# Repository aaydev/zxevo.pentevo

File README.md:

# Компьютер-конструктор ZX Evolution     

##### Компьютер-конструктор ZX Evolution!

#### [english](http://nedopc.com/zxevo/zxevo_eng.php)

**ВНИМАНИЕ!** **Изделие поставляется независимым производителем. Обращаться по поводу приобретения к Виталию [tetroid@inbox.ru](mailto:tetroid@inbox.ru).**

- - -

Компьютер конструктор **ZX Evolution** является развитием Spectrum-совместимых компьютеров, но собран на современной элементной базе и под современную периферию.

**Разработка:**  
hardware: Вадим Акимов (LVD), Чунин Роман (CHRV), Дмитриев Дмитрий (DDP);  
software: Вячеслав Савенков (Savelij).

### Характеристики:

*   Z80 3.5 МГц (классический)/ 7 МГц (турбо режим без WAIT)/ 14МГц (мега турбо режим с WAIT);
*   4 МБ ОЗУ, 512КБ ПЗУ;
*   Форм-фактор miniITX (microATX для rev.A и B), 2 слота ZXBUS, питание ATX или +5,+12В;
*   Гибкая архитектура, основанная на fpga (EP1K50);
*   Периферийный контроллер ATMEGA128;
*   PS/2 интерфейс клавиатуры и мыши;
*   Интерфейсы Floppy (1818ВГ93), IDE (один канал, два устройства master/slave), SD(HC) карта, RS232;
*   Видеовыходы RGB, VGA (аппаратный скандаблер);
*   Звуковые интерфейсы AY, Beeper, Covox (аппаратный ШИМ);
*   Поддержка механической клавиатуры и джойстика;
*   Поддержка Tape интерфейса (магнитофонный вход/выход);
*   Энергонезависимые часы/календарь.

Список мониторов протестированных на совместимость с ZX Evolution в VGA режиме [здесь](http://svn.nedopc.com/dl.php?repname=pentevo&path=%2Fdocs%2Fsupported_monitors.pdf).

Тестовая программа для PC для тестирования монитора на совместимость [здесь](http://nedopc.com/zxevo/tools/zxevo_vga_test_20100221.rar).

### Документация:

**_Форум поддержки пользователей_** [здесь](http://forum.nedopc.com/).

Принципиальная схема (revision C) [здесь](http://nedopc.com/zxevo/zxevo_sch_revc.pdf).

Монтажная схема (revision C) [здесь](http://nedopc.com/zxevo/zxevo_mon_revc.pdf).

Cписок деталей (revision C) [здесь](http://nedopc.com/zxevo/zxevo_bom_revc.pdf).

Руководство пользователя (revision C) [здесь](http://nedopc.com/zxevo/zxevo_user_manual_revc.pdf).

Руководство по сборке платы (revision C) [здесь](http://nedopc.com/zxevo/zxevo_solder_revc.pdf).

Документация для производства (revision C) [здесь](http://nedopc.com/zxevo/zxevo_revc.zip) \[PCAD2002\] (использование в коммерческих целях только по договоренности с представителями [NedoPC](http://nedopc.com/aboutus.php)).

**ЦЕНЫ:** [здесь](http://nedopc.com/catalog.php).

**Внимание!**  
Описание стартового меню (EVO RESET SERVICE), документация программиста (для конфигурации BASECONF) и документация по процедуре обновления прошивок (BOOTLOADER) находится в таблице **"Прошивки и Документация"**

### Прошивки и Документация:

|     |     |     |     |     |     |
| --- | --- | --- | --- | --- | --- |
| **Название** | **Версия** | **Назначение** | **Документация** | **Файлы** | **SVN** |
| **_EVO RESET SERVICE FE,  <br>EVO DOS FE,  <br>EVO PROF_** | latest | Улучшен эмулятор дисководов, теперь он работает с неизменной пзу TR-DOS.  <br>Для работы требуется соответствующая прошивка FPGA  <br>Стартовое меню, сервисные расширения и ZX ПЗУ.  <br>Предназначена для прошивки в ROM.  <br>_Прошивку можно произвести из предыдущей версии или с помощью **TEST&SERVICE**._  <br>Поддержка: Savelij. | [Описание сервис-прошивки ''EVO Reset Service''.pdf](http://svn.nedopc.com/filedetails.php?repname=pentevo&path=%2Fdocs%2F%D0%9E%D0%BF%D0%B8%D1%81%D0%B0%D0%BD%D0%B8%D0%B5+%D1%81%D0%B5%D1%80%D0%B2%D0%B8%D1%81-%D0%BF%D1%80%D0%BE%D1%88%D0%B8%D0%B2%D0%BA%D0%B8+%27%27EVO+Reset+Service%27%27.pdf) |     | [zxevo\_fe.rom](http://svn.nedopc.com/filedetails.php?repname=pentevo&path=%2From%2Fzxevo_fe.rom) |
| **_BASECONF FE_** | latest | Основная рабочая конфигурация (от NedoPC).  <br><br>*   Поддержка эмуляции портов дисковода/ВГ93, для использования этой фичи нужен ROM zxevo\_fe.rom.<br>*   Добавлена палитра DDP без ШИМа (alone).<br>*   Ускорена работа процессора на 14 МГц (psk7).<br><br>Предназначена для прошивки в ATMEGA128.  <br>_Прошивка производится с помощью **BOOTLOADER**._  <br>Поддержка: CHRV (ATMEGA128), LVD (EP1K50QC208). | [zxevo\_base\_configuration.odt](http://svn.nedopc.com/filedetails.php?repname=pentevo&path=%2Fdocs%2Fzxevo_base_configuration.odt)<br><br>[zxevo\_base\_configuration.pdf](http://svn.nedopc.com/filedetails.php?repname=pentevo&path=%2Fdocs%2Fzxevo_base_configuration.pdf) |     | [zxevo\_fw.bin](http://svn.nedopc.com/filedetails.php?repname=pentevo&path=%2Fcfgs%2Fstandalone_base_trdemu%2Ftrunk%2Fzxevo_fw.bin) |
| **_BOOTLOADER_** | 2012.01.24 | Загружает и обновляет рабочие конфигурации.  <br>Предназначена для прошивки в ATMEGA128.  <br>_Прошивка производится с помощью программатора._  <br>Поддержка: DDp. | [zxevo\_firmware\_update.pdf](http://nedopc.com/zxevo/rom/zxevo_firmware_update.pdf) | [bootloader20120124.zip](http://nedopc.com/zxevo/rom/bootloader20120124.zip) | [zxevo\_bl.hex](http://svn.nedopc.com/filedetails.php?repname=pentevo&path=%2Favrboot%2Ftrunk%2Favr%2Fzxevo_bl.hex)<br><br>[zxevo\_bl.e2p](http://svn.nedopc.com/filedetails.php?repname=pentevo&path=%2Favrboot%2Ftrunk%2Favr%2Fzxevo_bl.e2p)<br><br>[read\_me.txt](http://svn.nedopc.com/filedetails.php?repname=pentevo&path=%2Favrboot%2Ftrunk%2Fread_me.txt) |
| **_TEST&SERVICE_** | 2016.01.04 | Cервисная конфигурация для тестирования и настройки ZXEvo. Полезная конфигурация для тех кто сам собирает ZXEvo.  <br>Предназначена для прошивки в ATMEGA128.  <br>_Прошивка производится с помощью **BOOTLOADER**._  <br>Поддержка: DDp. | [zxevo\_testservice.pdf](http://nedopc.com/zxevo/rom/zxevo_testservice.pdf)  <br>[zxevo\_testservice\_flash.pdf](http://nedopc.com/zxevo/rom/zxevo_testservice_flash.pdf) | [testservice20160104.zip](http://nedopc.com/zxevo/rom/testservice20160104.zip) | [zxevo\_fw.bin](http://svn.nedopc.com/filedetails.php?repname=pentevo&path=%2Ftest_n_service%2Ftrunk%2Frus%2Fzxevo_fw.bin) |

Зеркало исходников (SVN) доступно на сайте [**ZXEVO.RU**.](http://svn.zxevo.ru/listing.php?repname=pentevo)

### Прошивки сторонних разработчиков:

**ВНИМАНИЕ:** Вопросы по поддержке прошивок задавайте непосредственно авторам прошивок. NedoPC не несет ответственности за ошибки или недоработки в прошивках сторонних разработчиков.

|     |     |     |     |     |
| --- | --- | --- | --- | --- |
| **Название** | **Версия** | **Назначение** | **Документация** | **Файлы** |
| [**_ZXEVO TS_**](http://forum.tslabs.info/viewtopic.php?f=12&t=20) |     | ZXEVO TS конфигурация с поддержкой спрайтов и оригинальных расширенных видеорежимов. Полноценная рабочая конфигурации отличается не только схемой, но и ROM. Также под нее созданы специализированное утилиты, игры и прочее ПО. [Подробности здесь.](http://forum.tslabs.info/viewtopic.php?f=12&t=20) | [FAQ](http://forum.tslabs.info/viewtopic.php?f=12&t=157) | [Инструкция по установке конфигурации.](http://forum.nedopc.com/viewtopic.php?f=30&t=622&start=652) |
| **_ScorpEvo_** | 6.1 (05.11.2011) | Scorpion Evolution (ScorpEvo) задуман как полноценная альтернатива (в дальнейшем – замена) самого знаменитого и в то же время противоречивого петербургского компьютера «Scorpion ZS 256 turbo+» Сергея Зонова. | [scorpevo.pdf](http://nedopc.com/zxevo/scorpion/scorpevo.pdf) | [scorpevo061.zip](http://nedopc.com/zxevo/scorpion/scorpevo061.zip)  <br>[svn scorpevo](http://svn.nedopc.com/listing.php?repname=pentevo&path=%2Fscorpevo%2F) |

- - -

### История версий:

**Revision C:**  
Изменения от предыдущей версии:

*   Форм фактор miniITX (172x170mm);
*   Убран PAL кодер;
*   Добавлен принтерный интерфейс по стандарту AY-принтер;
*   Добавлено управление множителем частоты;
*   Добавлены аудиовходы (всего 3 аудиовхода);
*   Используется процессор Z80 в QFP корпусе;
*   Убран отдельный RGB разъем (все выведено на VGA);
*   Добавлен RS232-USB мост;
*   Убран AT разъем питания;
*   Добавлен разъем для подключения PAL кодера.

**Revision B:**  
Изменения от предыдущей версии:

*   Исправлен шаблон PS/2 клавиатуры-мыши;
*   Исправлен ОЕ на ICS501;
*   Увеличена площадь радиатора 78M05;
*   Добавлен джампер регулирующий присутствие 12V на слотах;
*   Добавлены направляющие для разъема ATX питания;
*   Увеличены контактные площадки дросселей;
*   Уменьшен размер платы;
*   Убран джампер разрешающий програмирование контроллера;
*   Сделано для диодов 4148 универсальная площадка (на смд и выводные);
*   Для ZXBUS сделан указатель 1-го вывода;
*   Исправлена ошибка сброса ВГ93 (завел VG\_RES на D19);
*   Сделан ключ разъема FDD как на ПЦ платах (5-ый контакт);
*   Добавлены на плату надписи "HDD Led", "PWR Led", "ZX Keyboard/ZX Joystick", "Slot1", "Slot2";
*   Перемещен разъем VGA, чтобы был паралельно RGB-out.

Принципиальная схема (revision B) [здесь](http://nedopc.com/zxevo/zxevo_sch_revb.pdf).

Монтажная схема (revision B) [здесь](http://nedopc.com/zxevo/zxevo_mon_revb.pdf).

Cписок деталей (revision B) [здесь](http://nedopc.com/zxevo/zxevo_bom_revb.pdf).

Доработка для работы с принтером [AY-printer](http://nedopc.com/zxevo/zxevo_ay_printer.pdf).

Руководство пользователя (revision B) [здесь](http://nedopc.com/zxevo/zxevo_user_manual_revb.pdf).

Руководство по сборке платы (revision B) [здесь](http://nedopc.com/zxevo/zxevo_solderind_and_start_revb.pdf).

Документация для производства (revision B) [здесь](http://nedopc.com/zxevo/zxevo_revb.zip) \[PCAD2002\] (использование в коммерческих целях только по договоренности с представителями [NedoPC](http://nedopc.com/aboutus.php)).

**Revision A:**  
Первая версия - экспериментальная, только у разработчиков.

Принципиальная схема (revision A) [здесь](http://nedopc.com/zxevo/zxevo_sch_reva.pdf).

Монтажная схема (revision A) [здесь](http://nedopc.com/zxevo/zxevo_mon_reva.pdf).

Cписок деталей (revision A) [здесь](http://nedopc.com/zxevo/zxevo_detali_reva.pdf).

Документация для производства (revision A) [здесь](http://nedopc.com/zxevo/zxevo_reva.zip) \[PCAD2002\] (использование в коммерческих целях только по договоренности с представителями [NedoPC](http://nedopc.com/aboutus.php)).

- - -

Email: [nedopc@mail.ru](mailto:nedopc@mail.ru), [nedopc@yandex.ru](mailto:nedopc@yandex.ru).

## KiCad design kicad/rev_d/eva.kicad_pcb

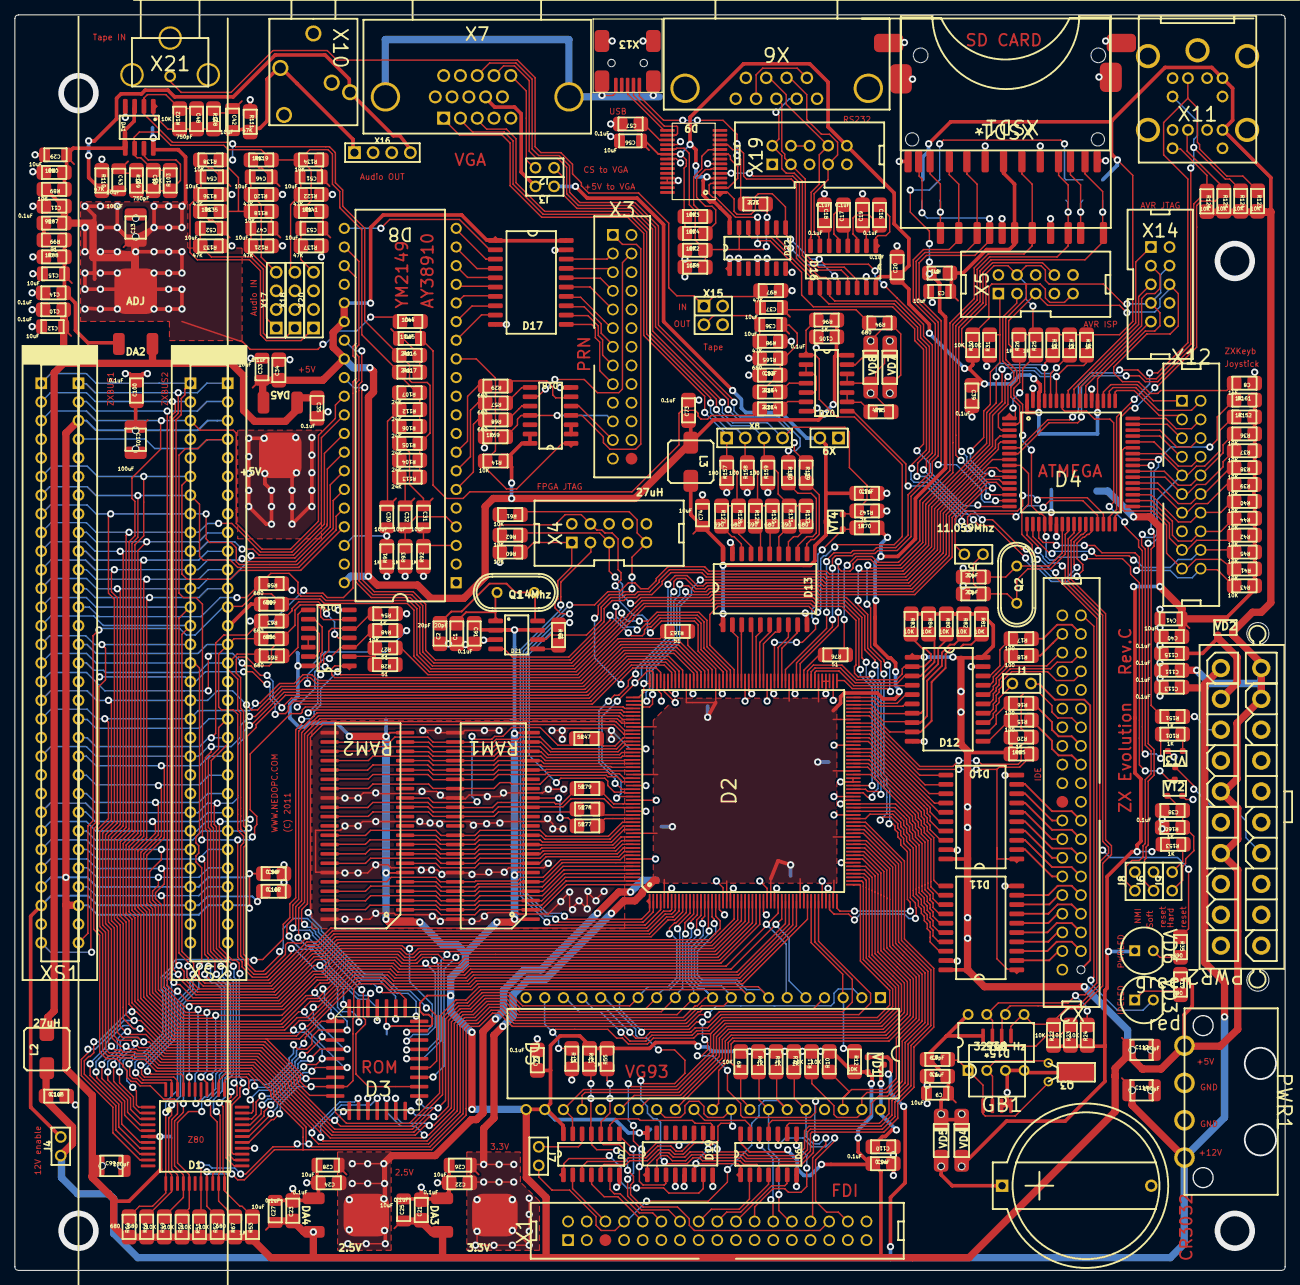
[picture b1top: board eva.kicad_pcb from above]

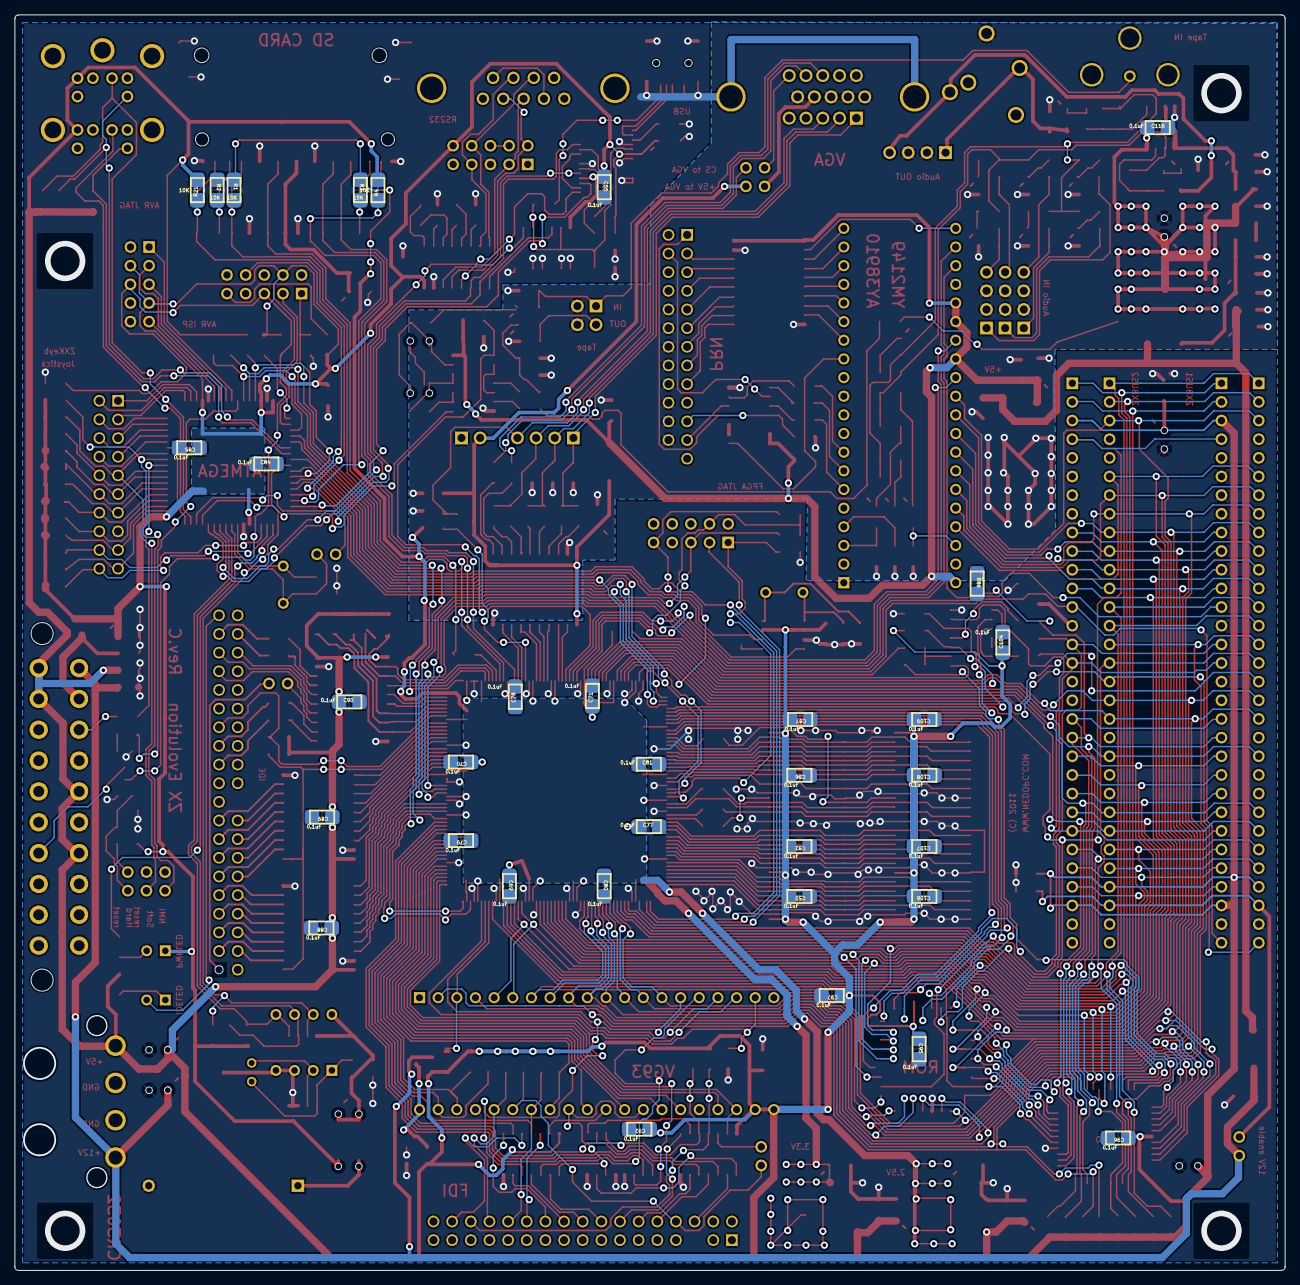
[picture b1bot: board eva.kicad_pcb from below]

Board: 2 copper layers, 173.0 x 171.0 mm, 338 parts (34 on the bottom side), 412 nets.

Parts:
C1, C2, C4, C5: 20pF; C-CHIP
C3, C9, C12, C15, C25, C26, C27, C28, C29, C30, C31, C32, C33, C36, C37, C41, C42, C43, C45, C46, C47, C51, C52, C53, C54, C56, C74: 10uF; EC-CHIP
C6, C10, C11, C14, C16, C17, C18, C19, C20, C21, C22, C23, C24, C34, C35, C38, C39, C40, C50, C55, C57, C69, C70, C71, C73, C76, C77, C78, C79, C80, C81, C82, C83, C84, C85, C86, C87, C88, C89, C90, C91, C92, C93, C94, C95, C96, C97, C98, C100, C102, C103, C104, C105, C106, C107, C108, C109, C110, C111, C113, C115, C116: 0.1uF; C-CHIP
C7: 6.8pF; C-CHIP
C8, C58: 1nF; C-CHIP
C13, C99, C101, C112, C114: 100uF; EC-CHIPB
C44: 10nF; C-CHIP
C48, C49: 750pF; C-CHIP
D1: QFP44X8
D2: PQFP208X5
D3: PLCC32
D4: TQFP64X8
D5, D8: DIP40
D6, D7, D20: SO14
D9: SSOP28
D10, D11, D12: SOL20
D13, D17: 74hct245; SOL20
D14: 74ACT04; SO14
D15: DIP8
D15*: PCF8583T
D16, D19: SO16
D18: 74HCT04; SO14
D21: SO8
D22: 74HCT125; SO14
DA1: SO8
DA2: ADJ; DPAK
DA3: 3.3V; DPAK
DA4: 2.5V; DPAK
DA5: +5V; DPAK
GB1: CR3032; BAT_Primary
J1, J2, J3, J4, J5, J6, J7, J8, J9: JUMPER_JUMPER(Primary)
L1: 1uH; L-CHIP
L2, L3: 27uH; CDR64B
PWR1: THP_4MR
PWR2: ATXPOWER
Q1: 14Mhz; CRYSTAL_QUARTZ(Primary)
Q2: 11.059Mhz; CRYSTAL_QUARTZ(Primary)
Q3: 32768 Hz; 32768
R1, R2, R3, R4, R9, R10, R11, R12, R14, R21, R22, R23, R24, R30, R31, R36, R37, R38, R39, R40, R41, R42, R43, R44, R45, R48, R49, R50, R51, R52, R60, R61, R62, R72, R73, R74, R80, R81, R82, R83, R84, R85, R89, R90, R102, R103, R118, R119, R123, R124, R125, R126, R134, R135, R138, R141: 10K; R-CHIP
R5, R6, R7, R8, R13, R20, R25, R26, R32, R33, R34, R53, R54, R55, R69, R70, R88, R91, R92, R93, R96, R101, R151, R152, R153, R160, R161: 1K; R-CHIP
R15, R16, R17, R18, R157, R158, R159: 100; R-CHIP
R19, R35, R127, R129, R131: 390; R-CHIP
R27, R28, R46, R47, R76, R77, R78, R79, R108, R109, R163: 51; R-CHIP
R29, R56, R57, R58, R59, R63, R64, R65, R66, R67, R68, R94, R128, R130, R132, R165: 680; R-CHIP
R71, R114, R164: 2.2K; R-CHIP
R86: 1; R-CHIP
R87, R99: 91; R-CHIP
R95, R97, R98, R110, R111, R120, R121, R122, R133, R136, R137: 47K; R-CHIP
R104, R105, R106, R107, R112, R113, R116, R117: 24K; R-CHIP
R139, R140, R142: 75; R-CHIP
RAM1, RAM2: SOJ42
VD1, VD2: SOT-23
VD3: red; LED100_LED(Primary)
VD4, VD5, VD7, VD8: LL4148
VD6: green; LED100_LED(Primary)
VT2, VT3, VT4: SOT-23
X1: FDD34M
X2: IDE40M
X3: IDC26
X4, X5, X14, X19: IDC10M
X6: DSUB-9
X7: DB15VGA
X8, X16, X17, X18, X20: PLB1-4I
X9: PLB1-2
X10: AYout; ST-214C
X11: MDD-6FR
X12: IDC20
X13: MINI-USB
X15: PLB2-2
X21: RSA103
XS1, XS2: SLOT62_ZXSLOT(Primary)
XSD1: SDC09W4
XSD1*: SD01-AP0003

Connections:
A0: D1.27, D2.44, D3.12, XS1.A9, XS2.A9
A1: D1.28, D2.41, D3.11, XS1.A10, XS2.A10
A2: D1.29, D2.40, D3.10, XS1.A11, XS2.A11
A3: D1.30, D2.39, D3.9, XS1.A12, XS2.A12
A4: D1.31, D2.38, D3.8, XS1.A24, XS2.A24
A5: D1.32, D2.37, D3.7, D5.5, XS1.A23, XS2.A23
A6: D1.34, D2.36, D3.6, D5.6, XS1.A22, XS2.A22
A7: D1.35, D2.31, D3.5, XS1.A21, XS2.A21
A8: D1.36, D2.30, D3.27, XS1.B26, XS2.B26
A9: D1.37, D2.29, D3.26, XS1.A27, XS2.A27
A10: D1.38, D2.28, D3.23, XS1.B27, XS2.B27
A11: D1.40, D2.27, D3.25, XS1.A28, XS2.A28
A12: D1.41, D2.26, D3.4, XS1.A2, XS2.A2
A13: D1.42, D2.25, D3.28, XS1.B2, XS2.B2
A14: D1.43, D2.24, XS1.A1, XS2.A1
A15: D1.44, D2.19, XS1.B1, XS2.B1
AGND: C10.2, C11.2, C12.2, C13.2, C14.2, C15.2, C29.2, C33.2, C34.2, C35.2, C73.2, C74.2, C76.2, C83.1, C105.2, C116.2, D8.1, D8.24, D13.10, D13.19, D17.10, D17.19, D18.7, D20.7, DA1.4, DA5.2, R69.1, R86.1, R88.1, R90.1, R91.1, R92.1, R93.1, R97.1, R98.1, R110.1, R111.1, R120.1, R121.1, R122.1, R133.1, R136.1, R137.1, R142.1, R157.1, R158.1, R159.1, R165.2, X3.10, X3.12, X3.14, X3.16, X3.18, X3.20, X3.22, X3.24, X7.6, X7.7, X7.8, X7.10, X7.11, X9.1, X10.1, X15.2, X15.4, X16.2, X16.3, X17.2, X17.3, X18.2, X18.3, X20.2, X20.3, X21.2, X21.3, X21.4
ATX_POWERON: R101.1, VT3.1
AVCC5: C33.1, C34.1, C73.1, C105.1, D8.25, D8.26, D8.28, D8.40, D17.1, D17.20, D18.13, D18.14, D20.14, DA5.3, L3.2, R14.1, R96.1
AVCC8: C11.1, C13.1, C44.1, C116.1, DA1.8, DA2.2, R87.2, R89.2
AYA0: D8.21, D17.2
AYA1: D8.20, D17.3
AYA2: D8.19, D17.4
AYA3: D8.18, D17.5
AYA4: D8.17, D17.6
AYA5: D8.16, D17.7
AYA6: D8.15, D17.8
AYA7: D8.14, D17.9
AYB0: D8.13, D18.1, R14.2
AYB5: D8.8, R29.2
AYB6: D8.7, R57.2
AYB7: D8.6, R68.2
AY_BC1: D2.136, D8.29
AY_BDIR: D2.135, D8.27
AY_CLK: D2.134, D8.22
BEEP: D2.133, D20.1, R96.2
CHA: C32.2, D8.4, R93.2
CHB: C31.2, D8.3, R92.2
CHC: C30.2, D8.38, R91.2
CLKZ: D1.1, R28.1
CLKZ_IN: D2.79, R27.1
CLKZ_OUT: D14.1, R163.2
CONFDONE: D2.2, D4.59, R34.2
CSROM: D2.150, D14.5, R54.2
CTS: D16.8, X6.8, X19.8
CTS_TTL: D4.16, D9.3, D22.11
D0: D1.9, D2.18, D3.13, D5.7, D8.37, XS1.B6, XS2.B6
D1: D1.10, D2.17, D3.14, D5.8, D8.36, XS1.B7, XS2.B7
D2: D1.7, D2.16, D3.15, D5.9, D8.35, XS1.B8, XS2.B8
D3: D1.3, D2.15, D3.17, D5.10, D8.34, XS1.B11, XS2.B11
D4: D1.2, D2.14, D3.18, D5.11, D8.33, XS1.B12, XS2.B12
D5: D1.4, D2.13, D3.19, D5.12, D8.32, XS1.B10, XS2.B10
D6: D1.5, D2.12, D3.20, D5.13, D8.31, XS1.B9, XS2.B9
D7: D1.8, D2.11, D3.21, D5.14, D8.30, XS1.B3, XS2.B3
DAT1: R2.2, XSD1.8, XSD1*.8
DAT2: R3.2, XSD1.9, XSD1*.9
DIR: D5.16, D6.3
FCLK: D2.183, R46.1
GND: C1.1, C2.1, C3.2, C4.1, C5.1, C6.1, C8.1, C9.2, C18.1, C19.2, C20.2, C21.2, C22.2, C23.2, C24.2, C25.2, C26.2, C27.2, C28.2, C38.2, C39.2, C40.2, C41.2, C50.1, C55.2, C56.2, C57.2, C58.1, C69.2, C70.2, C71.2, C77.2, C78.2, C79.2, C80.2, C81.2, C82.1, C84.2, C85.2, C86.1, C87.1, C88.2, C89.2, C90.2, C91.2, C92.2, C93.2, C94.2, C95.2, C96.2, C97.2, C98.2, C99.2, C100.2, C101.2, C102.2, C103.2, C104.2, C106.1, C107.1, C108.1, C109.1, C110.1, C111.2, C112.2, C113.2, C114.2, C115.2, D1.26, D2.6, D2.20, D2.23, D2.32, D2.35, D2.43, D2.49, D2.59, D2.76, D2.81, D2.82, D2.107, D2.108, D2.109, D2.117, D2.123, D2.129, D2.137, D2.145, D2.151, D2.154, D2.171, D2.181, D2.188, D3.16, D4.22, D4.53, D4.63, D5.20, D5.37, D6.7, D7.7, D9.7, D9.18, D9.21, D9.25, D9.26, D10.10, D10.19, D11.10, D11.19, D12.10, D12.19, D14.7, D15.3, D15.4, D15*.3, D15*.4, D16.15, D19.4, D19.5, D19.8, D21.3, D22.1, D22.2, D22.4, D22.5, D22.7, DA3.1, DA4.1, GB1.2, J6.1, J8.1, PWR1.2, PWR1.3, PWR2.3, PWR2.5, PWR2.7, PWR2.13, PWR2.15, PWR2.16, PWR2.17, Q3.3, R13.2, R31.1, R54.1, R58.1, R59.1, R60.2, R72.1, R86.2, R160.2, RAM1.22, RAM1.29, RAM1.37, RAM1.42, RAM2.22, RAM2.29, RAM2.37, RAM2.42, VT2.2, VT3.2, X1.1, X1.3, X1.7, X1.9, X1.11, X1.13, X1.15, X1.17, X1.19, X1.21, X1.23, X1.25, X1.27, X1.29, X1.31, X1.33, X2.2, X2.19, X2.22, X2.24, X2.26, X2.30, X2.40, X4.2, X4.10, X5.2, X5.10, X6.5, X6.10, X6.11, X7.16, X7.17, X11.3, X11.9, X11.13, X11.14, X11.15, X11.16, X11.17, X12.15, X13.5, X13.6, X13.7, X13.8, X13.9, X14.2, X14.10, X19.5, XS1.A6, XS1.A7, XS1.A14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
IA0: D12.15, X2.35
IA1: D12.14, X2.33
IA2: D12.16, X2.36
ID0: D10.9, X2.17
ID1: D10.7, X2.15
ID2: D10.5, X2.13
ID3: D10.3, X2.11
ID4: D11.9, X2.9
ID5: D11.7, X2.7
ID6: D11.5, X2.5
ID7: D11.3, X2.3
ID8: D11.2, X2.4
ID9: D11.4, X2.6
ID10: D11.6, X2.8
ID11: D11.8, X2.10
ID12: D10.2, X2.12
ID13: D10.4, X2.14
ID14: D10.6, X2.16
ID15: D10.8, X2.18
IDE_A0: D2.104, D12.5
IDE_A1: D2.103, D12.6
IDE_A2: D2.111, D12.4
IDE_D0: D2.96, D10.11
IDE_D1: D2.94, D10.13
IDE_D2: D2.92, D10.15
IDE_D3: D2.89, D10.17
IDE_D4: D2.87, D11.11
IDE_D5: D2.85, D11.13
IDE_D6: D2.75, D11.15
IDE_D7: D2.73, D11.17
IDE_D8: D2.71, D11.18
IDE_D9: D2.74, D11.16
IDE_D10: D2.83, D11.14
IDE_D11: D2.86, D11.12
IDE_D12: D2.88, D10.18
IDE_D13: D2.90, D10.16
IDE_D14: D2.93, D10.14
IDE_D15: D2.95, D10.12
IDE_DIR: D2.97, D10.1, D11.1, R85.2
IDE_RDY: D2.99, R20.1, X2.27
ILED: VD3.K, X2.39
IORQGE1: D2.78, R58.2, XS1.A13
IORQGE2: D2.80, R59.2, XS1.A31, XS2.A13
JOYD: D4.43, R41.2, X12.19
JOYF: D4.19, R43.2, X12.20
JOYL: D4.34, R44.2, X12.16
JOYR: D4.33, R42.2, X12.17
JOYU: D4.18, R45.2, X12.18
LOUT: C42.2, R111.2, X10.5, X16.1
NET00000: C110.2, D5.40, VD1.3
NET00001: C46.1, R119.1
NET00002: D2.189, R78.2
NET00003: C2.2, D21.8, Q1.A
NET00004: D2.190, R77.2
NET00005: D20.4, R164.2
NET00006: D2.168, R47.2
NET00007: D2.139, R163.1
NET00008: X6.4, X6.6
NET00009: R19.2, VD3.A
NET00010: X19.4, X19.6
NET00011: C47.1, R118.1
NET00012: C1.2, D21.1, Q1.B
NET00013: D14.2, R27.2, R28.2
NET00014: D4.17, R35.1
NET00015: J2.1, X7.15
NET00016: R35.2, VD6.K
NET00017: D7.12, J7.0
NET00018: C46.2, R120.2, X17.4
NET00019: D20.6, R114.2
NET00020: D2.114, R76.2
NET00021: C47.2, R121.2, X17.1
NET00022: C51.2, R122.2, X18.4
NET00023: C52.2, R133.2, X18.1
NET00024: D4.58, R101.2
NET00025: C48.1, DA1.2, R102.2, R104.1, R105.1, R113.1, R116.1, R118.2, R135.2, R138.1
NET00026: C48.2, DA1.1, R102.1, R108.2
NET00027: R87.1, R99.2
NET00028: D20.11, D20.12, R95.2, VD7.2, VD8.1
NET00029: D21.5, R46.2
NET00030: D20.9, D20.10, R95.1
NET00031: C49.1, DA1.6, R103.2, R106.1, R107.1, R112.1, R117.1, R119.2, R134.2, R141.1
NET00032: C49.2, DA1.7, R103.1, R109.2
NET00033: C51.1, R134.1
NET00034: C32.1, R104.2, R113.2
NET00035: C37.1, R94.2
NET00036: D14.8, R65.1
NET00037: D9.16, X13.2
NET00038: D20.13, R94.1, VD7.1, VD8.2
NET00039: D18.6, R29.1
NET00040: D18.8, R57.1
NET00041: C10.1, C12.1, C35.1, DA2.3, DA5.1, L2.1
NET00042: C52.1, R135.1
NET00043: D18.10, R68.1
NET00044: D2.186, R79.2
NET00045: C30.1, R107.2, R112.2
NET00046: C14.1, C15.1, DA2.1, R88.2, R99.1
NET00047: C31.1, R105.2, R106.2
NET00048: C42.1, R108.1
NET00049: C43.1, R109.1
NET00050: J9.1, R153.1
NET00051: C53.2, R137.2, X20.4
NET00052: C54.2, R136.2, X20.1
NET00053: C17.2, D16.5
NET00054: C17.1, D16.4
NET00055: C16.2, D16.3
NET00056: C16.1, D16.1
NET00057: C18.2, D16.6
NET00058: C19.1, D16.2
NET00059: C54.1, R138.2
NET00060: C44.2, C45.2, R114.1
NET00061: C45.1, R116.2, R117.2
NET00062: C53.1, R141.2
NET00063: C38.1, J9.0, R160.1, VT2.1
NET00064: D12.13, J1.0
NET00065: R71.1, X13.1
NET00066: D9.15, X13.3
NET00067: GB1.1, VD5.1
NET00068: D12.17, R18.2
NET00069: D13.11, R139.2
NET00070: D13.12, R140.2
NET00071: D4.40, R151.2
NET00072: PWR2.14, VT3.3
NET00074: D16.12, D22.9
NET00075: D18.2, D18.3
NET00076: D12.18, R17.2
NET00077: D16.9, D22.12
NET00078: D9.2, D9.9
NET00079: C57.1, D9.17
NET00080: D9.6, R74.2
NET00081: D9.10, R73.2
NET00085: J3.1, X7.9
NET00087: C36.1, C83.2, R164.1, R165.1
NET00100: D14.11, D14.12
NET00101: D14.4, R63.1
NET00105: D12.11, R15.2
NET00106: D14.10, D14.13
NET00107: D12.12, R16.2
NMIKEY: D4.41, J8.0, R161.1
OUT_B: R131.1, R132.1, R159.2, X7.3, X8.3
OUT_CS: J2.0, R142.2, VT4.2, X8.4
OUT_G: R129.1, R130.1, R158.2, X7.2, X8.2
OUT_HS: R140.1, X7.13
OUT_R: R127.1, R128.1, R157.2, X7.1, X8.1
OUT_VS: R139.1, X7.14
PLLS0: D4.4, D21.6
PLLS1: D4.5, D21.4
PRGDI: D4.2, R30.2, X5.9
PRGDO: D4.3, X5.3
PRGEXCLOCK: J5.1, X5.8
PRN_D0: D17.18, X3.3
PRN_D1: D17.17, X3.5
PRN_D2: D17.16, X3.7
PRN_D3: D17.15, X3.9
PRN_D4: D17.14, X3.11
PRN_D5: D17.13, X3.13
PRN_D6: D17.12, X3.15
PRN_D7: D17.11, X3.17
PR_BUSY: D18.11, R69.2, X3.21
PR_ERR: D18.9, X3.4
PR_PE: D18.5, X3.23
PR_STRB: D18.4, X3.1
PS2_KEYB_CLK: D4.6, R124.1, X11.5
PS2_KEYB_DAT: D4.31, R123.1, X11.1
PS2_MOUS_CLK: D4.7, R126.1, X11.11
PS2_MOUS_DAT: D4.32, R125.1, X11.7
PWRGOOD: PWR2.8, R151.1
RA0: D2.177, RAM1.17, RAM2.17
RA1: D2.175, RAM1.18, RAM2.18
RA2: D2.173, RAM1.19, RAM2.19
RA3: D2.170, RAM1.20, RAM2.20
RA4: D2.169, RAM1.23, RAM2.23
RA5: D2.172, RAM1.24, RAM2.24
RA6: D2.174, RAM1.25, RAM2.25
RA7: D2.176, RAM1.26, RAM2.26
RA8: D2.179, RAM1.27, RAM2.27
RA9: D2.180, RAM1.28, RAM2.28
RD0: D2.208, RAM1.2, RAM2.2
RD1: D2.206, RAM1.3, RAM2.3
RD2: D2.204, RAM1.4, RAM2.4
RD3: D2.202, RAM1.5, RAM2.5
RD4: D2.199, RAM1.7, RAM2.7
RD5: D2.197, RAM1.8, RAM2.8
RD6: D2.195, RAM1.9, RAM2.9
RD7: D2.192, RAM1.10, RAM2.10
RD8: D2.191, RAM1.33, RAM2.33
RD9: D2.193, RAM1.34, RAM2.34
RD10: D2.196, RAM1.35, RAM2.35
RD11: D2.198, RAM1.36, RAM2.36
RD12: D2.200, RAM1.38, RAM2.38
RD13: D2.203, RAM1.39, RAM2.39
RD14: D2.205, RAM1.40, RAM2.40
RD15: D2.207, RAM1.41, RAM2.41
RES: D2.142, D14.3, R48.2
ROMPG2: D2.164, D3.2
ROMPG3: D2.163, D3.30
ROMPG4: D2.162, D3.1
ROUT: C43.2, R110.2, X10.2, X16.4
RS: D3.29, R65.2, XS1.A16, XS2.A16
RTC_PWR: C6.2, C7.1, C9.1, D15.8, D15*.8, VD4.2, VD5.2
RTC_X1: C7.2, D15.1, D15*.1, Q3.1
RTC_X2: D15.2, D15*.2, Q3.2
RTS: D16.7, X6.7, X19.7
RTS_TTL: D4.30, D9.11, D16.10
RXD: D16.13, X6.2, X19.2
RXD_TTL: D4.27, D9.1, D22.8
SCL: D4.25, D15.6, D15*.6, R23.2
SDA: D4.26, D15.5, D15*.5, R22.2
SDCLK: R76.1, XSD1.5, XSD1*.5
SDDET: D4.15, R4.1, XSD1.11, XSD1*.11
SDDI: D2.115, R1.2, XSD1.7, XSD1*.7
SDDO: D2.116, XSD1.2, XSD1*.2
SDWPR: D4.14, R21.1, XSD1.12, XSD1*.10
SPICK: D2.155, D2.184, D4.11, R31.2, X5.1
SPIDI: D2.158, D4.13
SPIDO: D2.156, D2.157, D4.12
STEP: D2.46, D5.15, D6.5
TAPE_BIT: D4.29, D20.8
TAPE_IN: C37.2, R97.2, X15.1, X21.1
TAPE_OUT: C36.2, R98.2, X15.3
TCK_AVR: D4.57, X14.1
TCK_FPGA: D2.1, R60.1, X4.1
TDI_AVR: D4.54, X14.9
TDI_FPGA: D2.153, R61.1, X4.9
TDO_AVR: D4.55, X14.3
TDO_FPGA: D2.4, X4.3
TMS_AVR: D4.56, X14.5
TMS_FPGA: D2.50, R62.1, X4.5
TXD: D16.14, X6.3, X19.3
TXD_TTL: D4.28, D9.5, D16.11
USB_ENA: C58.2, D9.19, D22.10, D22.13, R71.2, R72.2
VB+: D13.14, R131.2
VB-: D13.13, R132.2
VCC2V5: C24.1, C28.1, C78.1, C79.1, C80.1, C81.1, D2.21, D2.33, D2.48, D2.72, D2.77, D2.91, D2.106, D2.124, D2.130, D2.152, D2.185, D2.201, DA4.2
VCC3V3: C22.1, C26.1, C69.1, C70.1, C71.1, C77.1, D2.5, D2.22, D2.34, D2.42, D2.51, D2.66, D2.84, D2.98, D2.110, D2.118, D2.138, D2.146, D2.165, D2.178, D2.194, DA3.2, L1.1, R1.1, R2.1, R3.1, R61.2, R62.2, R70.2, X4.4
VCC5: C21.1, C23.1, C25.1, C27.1, C50.2, C82.2, C86.2, C87.2, C88.1, C89.1, C90.1, C91.1, C92.1, C93.1, C94.1, C95.1, C96.1, C97.1, C98.1, C99.1, C100.1, C101.1, C104.1, C106.2, C107.2, C108.2, C109.2, C111.1, C112.1, D1.6, D3.32, D5.21, D5.22, D6.14, D7.14, D10.20, D11.20, D12.1, D12.20, D14.14, D19.16, D21.2, D21.7, DA3.3, DA4.3, PWR1.1, PWR2.4, PWR2.6, PWR2.19, PWR2.20, R4.2, R5.1, R6.1, R7.1, R8.1, R9.2, R10.2, R11.2, R12.2, R19.1, R20.2, R21.2, R32.1, R33.1, R34.1, R48.1, R49.1, R50.1, R51.1, R52.1, R53.1, R55.2, R64.1, R66.1, R67.1, R80.1, R81.1, R82.1, R83.1, R84.1, R85.1, R123.2, R124.2, R125.2, R126.2, RAM1.1, RAM1.6, RAM1.21, RAM2.1, RAM2.6, RAM2.21, VD1.2, VD2.2, X11.4, X11.10, XS1.A3, XS1.A29, XS1.B28, XS2.A3, XS2.A29, XS2.B28
VCC5_MEGA: C20.1, C39.1, C40.1, C41.1, C55.1, C56.1, C84.1, C85.1, D4.21, D4.52, D4.62, D4.64, D9.4, D9.20, D16.16, D22.14, R22.1, R23.1, R24.1, R25.2, R26.2, R30.1, R36.1, R37.1, R38.1, R39.1, R40.1, R41.1, R42.1, R43.1, R44.1, R45.1, R73.1, R74.1, R152.2, R153.2, R161.2, VD2.3, VD4.1, VD6.A, X5.4, X14.4, X14.7, X19.10
VCC5_STBY: C115.1, PWR2.9, VD2.1
VCC12: C103.1, C113.1, C114.1, J4.0, L2.2, PWR1.4, PWR2.10, VD1.1
VCC12S: C102.1, J4.1, XS1.B29, XS2.B29
VCCSD: C3.1, L1.2, XSD1.4, XSD1*.4
VCSYNC: D2.122, R70.1, VT4.1
VG+: D13.16, R129.2
VG-: D13.15, R130.2
VG_A0: D2.69, D19.1
VG_A1: D2.70, D19.2
VG_CLK: D2.56, D5.24
VG_DRQ: D2.63, D5.38, R10.1
VG_DS0: D7.3, D19.11
VG_DS1: D7.5, D19.10
VG_DS2: D7.9, D19.9
VG_DS3: D7.1, D19.7
VG_HRDY: D2.55, D5.23, D7.13
VG_IRQ: D2.64, D5.39, R11.1
VG_MOT: D5.28, D5.32, D6.1, D19.6
VG_RAWR: D2.58, D5.27
VG_RCLK: D2.57, D5.26
VG_SIDE: D2.65, D6.11
VG_SL: D2.47, D5.17
VG_SR: D2.53, D5.18
VG_TR43: D2.60, D5.29
VG_WD: D2.61, D5.31
VG_WF_DE: D2.62, D5.33, R9.1
VG_WRD: D2.67, D6.9
VHSYNC: D2.121, D13.8
VIDEOVCC: C74.1, C76.1, D13.1, D13.20, J3.0, L3.1, VT4.3, X9.2
VIRTGND: C29.1, DA1.3, DA1.5, R89.1, R90.2
VR+: D13.18, R127.2
VR-: D13.17, R128.2
VVSYNC: D2.120, D13.9
V_B+: D2.126, D13.6
V_B-: D2.125, D13.7
V_G+: D2.128, D13.4
V_G-: D2.127, D13.5
V_R+: D2.132, D13.2
V_R-: D2.131, D13.3
WG: D5.30, D6.13
XTAL1: C5.2, D4.24, J5.0, Q2.B
XTAL2: C4.2, D4.23, Q2.A
ZXCOL0: D4.35, R40.2, X12.14
ZXCOL1: D4.36, R39.2, X12.13
ZXCOL2: D4.37, R38.2, X12.12
ZXCOL3: D4.38, R37.2, X12.11
ZXCOL4: D4.39, R36.2, X12.10
ZXROW0: D4.51, X12.1
ZXROW1: D4.50, X12.2
ZXROW2: D4.49, X12.3
ZXROW3: D4.48, X12.4
ZXROW4: D4.47, X12.5
ZXROW5: D4.46, X12.6
ZXROW6: D4.45, X12.7
ZXROW7: D4.44, X12.8
~BEEP~: D20.2, D20.3, D20.5
~BUSA: D1.20, XS1.A26, XS2.A26
~BUSR: D1.22, R53.2, XS1.A19, XS2.A19
~CONFIG: D2.105, D4.61, R32.2
~CSROM: D14.6, R56.2, XS1.A25, XS2.A25
~DIR: D6.4, X1.18
~DOS: D2.160, D3.3, XS1.A4, XS2.A4
~DS0: D7.4, X1.10
~DS1: D7.6, X1.12
~DS2: D7.8, X1.14
~DS3: D7.2, X1.6
~HALT: D1.14, XS1.B15, XS2.B15
~ICS0: R17.1, X2.37
~ICS1: R18.1, X2.38
~IDE_CS0: D2.113, D12.2, R83.2
~IDE_CS1: D2.112, D12.3, R84.2
~IDE_RD: D2.101, D12.8, R82.2
~IDE_RS: D2.102, D12.7, R80.2
~IDE_WR: D2.100, D12.9, R81.2
~INT: D1.12, D2.10, R64.2, XS1.B13, XS2.B13
~IORQ: D1.16, D2.7, R50.2
~IORQ1: D2.148, XS1.B17
~IORQ2: D2.149, XS1.B31, XS2.B17
~IP: D5.35, J7.1, R5.2, X1.8
~IRD: R16.1, X2.25
~IWR: R15.1, X2.23
~M1: D1.24, D2.144, XS1.B24, XS2.B24
~MOT: D6.2, X1.16
~MREQ: D1.15, D2.8, R49.2, XS1.B16, XS2.B16
~NMI: D1.13, D2.9, R66.2, XS1.B14, XS2.B14
~PEN: D4.1, R25.1
~PRGRST: C8.2, D4.20, R26.1, VT2.3, X5.5, X14.6
~RD: D1.18, D2.141, D5.4, R51.2, XS1.B18, XS2.B18
~RDAT: D7.11, R8.2, X1.30
~RDAT_B: D2.68, D7.10, R55.1
~RDROM: D3.22, R56.1, XS1.A15, XS2.A15
~RES: D1.23, D8.23, R63.2, XS1.A20, XS2.A20
~RFSH: D1.25, D2.147, XS1.B25, XS2.B25
~RLCAS: R78.1, RAM1.31, RAM2.31
~ROMOE: D2.167, D3.24
~ROMPG0: D2.161, D14.9
~ROMWE: D2.166, D3.31
~RRAS0: R77.1, RAM1.14
~RRAS1: R47.1, RAM2.14
~RTCINT: D4.9, D15.7, D15*.7, R24.2
~RUCAS: R79.1, RAM1.30, RAM2.30
~RWE: D2.187, RAM1.13, RAM2.13
~SDCS: D2.119, XSD1.1, XSD1*.1
~SIDE: D6.10, X1.32
~SOFTRST~: D4.42, J6.0, R152.1, X12.9
~SPICS: D2.182, D4.10
~SPIINT: D2.159, D4.8
~STATUS: D2.52, D4.60, R33.2
~STEP: D6.6, X1.20
~TR00: D5.34, R6.2, X1.26
~VG_CS: D2.45, D5.3, R12.1
~VG_RES: D2.54, D5.19, D19.3, R13.1
~WAIT: D1.21, D2.143, R67.2, XS1.B21, XS2.B21
~WD: D6.8, X1.22
~WG: D6.12, X1.24
~WP: D5.36, R7.2, X1.28
~WR: D1.19, D2.140, D5.2, R52.2, XS1.B19, XS2.B19

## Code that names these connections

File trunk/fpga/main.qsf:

# Copyright (C) 1991-2006 Altera Corporation
# Your use of Altera Corporation's design tools, logic functions
# and other software and tools, and its AMPP partner logic
# functions, and any output files from any of the foregoing
# (including device programming or simulation files), and any
# associated documentation or information are expressly subject
# to the terms and conditions of the Altera Program License
# Subscription Agreement, Altera MegaCore Function License
# Agreement, or other applicable license agreement, including,
# without limitation, that your use is for the sole purpose of
# programming logic devices manufactured by Altera and sold by
# Altera or its authorized distributors.  Please refer to the
# applicable agreement for further details.


# The default values for assignments are stored in the file
#               main_assignment_defaults.qdf
# If this file doesn't exist, and for assignments not listed, see file
#               assignment_defaults.qdf

# Altera recommends that you do not modify this file. This
# file is updated automatically by the Quartus II software
# and any changes you make may be lost or overwritten.


set_global_assignment -name DEVICE "EP1K50QC208-3"
set_global_assignment -name FAMILY ACEX1K
set_global_assignment -name TOP_LEVEL_ENTITY main
set_global_assignment -name ORIGINAL_QUARTUS_VERSION 6.1
set_global_assignment -name PROJECT_CREATION_TIME_DATE "11:53:26  OCTOBER 02, 2009"
set_global_assignment -name LAST_QUARTUS_VERSION 6.1
set_global_assignment -name DEVICE_FILTER_PACKAGE "ANY QFP"
set_global_assignment -name DEVICE_FILTER_PIN_COUNT 208
set_global_assignment -name DEVICE_FILTER_SPEED_GRADE 3
set_location_assignment PIN_7 -to iorq_n
set_location_assignment PIN_8 -to mreq_n
set_location_assignment PIN_9 -to nmi_n
set_location_assignment PIN_10 -to int_n
set_location_assignment PIN_11 -to d[7]
set_location_assignment PIN_12 -to d[6]
set_location_assignment PIN_13 -to d[5]
set_location_assignment PIN_14 -to d[4]
set_location_assignment PIN_15 -to d[3]
set_location_assignment PIN_16 -to d[2]
set_location_assignment PIN_17 -to d[1]
set_location_assignment PIN_18 -to d[0]
set_location_assignment PIN_19 -to a[15]
set_location_assignment PIN_24 -to a[14]
set_location_assignment PIN_25 -to a[13]
set_location_assignment PIN_26 -to a[12]
set_location_assignment PIN_27 -to a[11]
set_location_assignment PIN_28 -to a[10]
set_location_assignment PIN_29 -to a[9]
set_location_assignment PIN_30 -to a[8]
set_location_assignment PIN_31 -to a[7]
set_location_assignment PIN_36 -to a[6]
set_location_assignment PIN_37 -to a[5]
set_location_assignment PIN_38 -to a[4]
set_location_assignment PIN_39 -to a[3]
set_location_assignment PIN_40 -to a[2]
set_location_assignment PIN_41 -to a[1]
set_location_assignment PIN_44 -to a[0]
set_location_assignment PIN_45 -to vg_cs_n
set_location_assignment PIN_46 -to step
set_location_assignment PIN_47 -to vg_sl
set_location_assignment PIN_53 -to vg_sr
set_location_assignment PIN_54 -to vg_res_n
set_location_assignment PIN_55 -to vg_hrdy
set_location_assignment PIN_56 -to vg_clk
set_location_assignment PIN_57 -to vg_rclk
set_location_assignment PIN_58 -to vg_rawr
set_location_assignment PIN_60 -to vg_tr43
set_location_assignment PIN_61 -to vg_wd
set_location_assignment PIN_62 -to vg_wf_de
set_location_assignment PIN_63 -to vg_drq
set_location_assignment PIN_64 -to vg_irq
set_location_assignment PIN_65 -to vg_side
set_location_assignment PIN_67 -to vg_wrd
set_location_assignment PIN_68 -to rdat_b_n
set_location_assignment PIN_69 -to vg_a[0]
set_location_assignment PIN_70 -to vg_a[1]
set_location_assignment PIN_71 -to ide_d[8]
set_location_assignment PIN_73 -to ide_d[7]
set_location_assignment PIN_74 -to ide_d[9]
set_location_assignment PIN_75 -to ide_d[6]
set_location_assignment PIN_78 -to iorqge1
set_location_assignment PIN_79 -to clkz_in
set_location_assignment PIN_80 -to iorqge2
set_location_assignment PIN_83 -to ide_d[10]
set_location_assignment PIN_85 -to ide_d[5]
set_location_assignment PIN_86 -to ide_d[11]
set_location_assignment PIN_87 -to ide_d[4]
set_location_assignment PIN_88 -to ide_d[12]
set_location_assignment PIN_89 -to ide_d[3]
set_location_assignment PIN_92 -to ide_d[2]
set_location_assignment PIN_93 -to ide_d[14]
set_location_assignment PIN_94 -to ide_d[1]
set_location_assignment PIN_95 -to ide_d[15]
set_location_assignment PIN_96 -to ide_d[0]
set_location_assignment PIN_97 -to ide_dir
set_location_assignment PIN_99 -to ide_rdy
set_location_assignment PIN_100 -to ide_wr_n
set_location_assignment PIN_101 -to ide_rd_n
set_location_assignment PIN_102 -to ide_rs_n
set_location_assignment PIN_103 -to ide_a[1]
set_location_assignment PIN_104 -to ide_a[0]
set_location_assignment PIN_111 -to ide_a[2]
set_location_assignment PIN_112 -to ide_cs1_n
set_location_assignment PIN_113 -to ide_cs0_n
set_location_assignment PIN_114 -to sdclk
set_location_assignment PIN_115 -to sddi
set_location_assignment PIN_116 -to sddo
set_location_assignment PIN_119 -to sdcs_n
set_location_assignment PIN_120 -to vvsync
set_location_assignment PIN_121 -to vhsync
set_location_assignment PIN_122 -to vcsync
set_location_assignment PIN_125 -to vblu[0]
set_location_assignment PIN_126 -to vblu[1]
set_location_assignment PIN_127 -to vgrn[0]
set_location_assignment PIN_128 -to vgrn[1]
set_location_assignment PIN_131 -to vred[0]
set_location_assignment PIN_132 -to vred[1]
set_location_assignment PIN_133 -to beep
set_location_assignment PIN_134 -to ay_clk
set_location_assignment PIN_135 -to ay_bdir
set_location_assignment PIN_136 -to ay_bc1
set_location_assignment PIN_139 -to clkz_out
set_location_assignment PIN_140 -to wr_n
set_location_assignment PIN_141 -to rd_n
set_location_assignment PIN_142 -to res
set_location_assignment PIN_143 -to wait_n
set_location_assignment PIN_144 -to m1_n
set_location_assignment PIN_147 -to rfsh_n
set_location_assignment PIN_148 -to iorq1_n
set_location_assignment PIN_149 -to iorq2_n
set_location_assignment PIN_150 -to csrom
set_location_assignment PIN_157 -to spido
set_location_assignment PIN_158 -to spidi
set_location_assignment PIN_159 -to spiint_n
set_location_assignment PIN_160 -to dos_n
set_location_assignment PIN_161 -to rompg0_n
set_location_assignment PIN_162 -to rompg4
set_location_assignment PIN_163 -to rompg3
set_location_assignment PIN_164 -to rompg2
set_location_assignment PIN_166 -to romwe_n
set_location_assignment PIN_167 -to romoe_n
set_location_assignment PIN_168 -to rras1_n
set_location_assignment PIN_169 -to ra[4]
set_location_assignment PIN_170 -to ra[3]
set_location_assignment PIN_172 -to ra[5]
set_location_assignment PIN_173 -to ra[2]
set_location_assignment PIN_174 -to ra[6]
set_location_assignment PIN_175 -to ra[1]
set_location_assignment PIN_176 -to ra[7]
set_location_assignment PIN_177 -to ra[0]
set_location_assignment PIN_179 -to ra[8]
set_location_assignment PIN_180 -to ra[9]
set_location_assignment PIN_182 -to spics_n
set_location_assignment PIN_183 -to fclk
set_location_assignment PIN_184 -to spick
set_location_assignment PIN_186 -to rucas_n
set_location_assignment PIN_187 -to rwe_n
set_location_assignment PIN_189 -to rlcas_n
set_location_assignment PIN_190 -to rras0_n
set_location_assignment PIN_191 -to rd[8]
set_location_assignment PIN_192 -to rd[7]
set_location_assignment PIN_193 -to rd[9]
set_location_assignment PIN_195 -to rd[6]
set_location_assignment PIN_196 -to rd[10]
set_location_assignment PIN_197 -to rd[5]
set_location_assignment PIN_198 -to rd[11]
set_location_assignment PIN_199 -to rd[4]
set_location_assignment PIN_200 -to rd[12]
set_location_assignment PIN_202 -to rd[3]
set_location_assignment PIN_203 -to rd[13]
set_location_assignment PIN_204 -to rd[2]
set_location_assignment PIN_205 -to rd[14]
set_location_assignment PIN_206 -to rd[1]
set_location_assignment PIN_207 -to rd[15]
set_location_assignment PIN_208 -to rd[0]
set_location_assignment PIN_90 -to ide_d[13]
set_instance_assignment -name CLOCK_SETTINGS "FPGA clock" -to fclk
set_instance_assignment -name GLOBAL_SIGNAL ON -to fclk
set_global_assignment -name FMAX_REQUIREMENT "28 MHz" -section_id "FPGA clock"
set_global_assignment -name GENERATE_RBF_FILE ON
set_global_assignment -name ON_CHIP_BITSTREAM_DECOMPRESSION OFF
set_global_assignment -name FLEX10K_DEVICE_IO_STANDARD LVTTL/LVCMOS
set_global_assignment -name VERILOG_FILE main.v
set_global_assignment -name ADD_DEFAULT_PINS_TO_SIMULATION_OUTPUT_WAVEFORMS OFF

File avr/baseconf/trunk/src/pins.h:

#ifndef PINS_H
#define PINS_H

/**
 * @file
 * @brief ATMEGA128 pins definition.
 * @author http://www.nedopc.com
 *
 * ATMEGA128 pins definition:
 * - define PIN number;
 * - define PORT register;
 * - define input PINs register;
 * - define Data Direction Register.
 */

/** nCONFIG fpga pin number. */
#define nCONFIG      PF0
/** nCONFIG fpga port register. */
#define nCONFIG_PORT PORTF
/** nCONFIG fpga pins register. */
#define nCONFIG_PIN  PINF
/** nCONFIG fpga direction register. */
#define nCONFIG_DDR  DDRF

/** nSTATUS fpga pin number. */
#define nSTATUS      PF1
/** nSTATUS fpga port register. */
#define nSTATUS_PORT PORTF
/** nSTATUS fpga pins register. */
#define nSTATUS_PIN  PINF
/** nSTATUS fpga direction register. */
#define nSTATUS_DDR  DDRF

/** CONF_DONE (configuration done) fpga pin number. */
#define CONF_DONE PF2
/** CONF_DONE (configuration done) fpga port register. */
#define CONF_DONE_PORT PORTF
/** CONF_DONE (configuration done) fpga pins register. */
#define CONF_DONE_PIN  PINF
/** CONF_DONE (configuration done) fpga direction register. */
#define CONF_DONE_DDR  DDRF

/** LED indicator pin number. */
#define LED      PB7
/** LED indicator port register. */
#define LED_PORT PORTB
/** LED indicator pins register. */
#define LED_PIN  PINB
/** LED indicator direction register. */
#define LED_DDR  DDRB

/** PS2 keyboard clock pin number. */
#define PS2KBCLK PE4
/** PS2 keyboard clock port register. */
#define PS2KBCLK_PORT PORTE
/** PS2 keyboard clock pins register. */
#define PS2KBCLK_PIN  PINE
/** PS2 keyboard clock direction register. */
#define PS2KBCLK_DDR  DDRE

/** PS2 keyboard data pin number. */
#define PS2KBDAT PD6
/** PS2 keyboard data port register. */
#define PS2KBDAT_PORT PORTD
/** PS2 keyboard data pins register. */
#define PS2KBDAT_PIN  PIND
/** PS2 keyboard data direction register. */
#define PS2KBDAT_DDR  DDRD

/** PS2 mouse clock pin number. */
#define PS2MSCLK PE5
/** PS2 mouse clock port register. */
#define PS2MSCLK_PORT PORTE
/** PS2 mouse clock pins register. */
#define PS2MSCLK_PIN  PINE
/** PS2 mouse clock direction register. */
#define PS2MSCLK_DDR  DDRE

/** PS2 mouse data pin number. */
#define PS2MSDAT PD7
/** PS2 mouse data port register. */
#define PS2MSDAT_PORT PORTD
/** PS2 mouse data pins register. */
#define PS2MSDAT_PIN  PIND
/** PS2 mouse data direction register. */
#define PS2MSDAT_DDR  DDRD

/** RS232 TXD pin number. */
#define RS232TXD PD3
/** RS232 TXD port register. */
#define RS232TXD_PORT PORTD
/** RS232 TXD pins register. */
#define RS232TXD_PIN  PIND
/** RS232 TXD direction register. */
#define RS232TXD_DDR  DDRD

/** Tape in pin number. */
#define TAPEIN PD4
/** Tape port register. */
#define TAPEIN_PORT PORTD
/** Tape pins register. */
#define TAPEIN_PIN  PIND
/** Tape direction register. */
#define TAPEIN_DDR  DDRD

/** nSPICS fpga pin number. */
#define nSPICS      PB0
/** nSPICS fpga port register. */
#define nSPICS_PORT PORTB
/** nSPICS fpga pins register. */
#define nSPICS_PIN  PINB
/** nSPICS fpga direction register. */
#define nSPICS_DDR  DDRB

/** ATX POWER ON pin number. */
#define ATXPWRON      PF3
/** ATX POWER ON port register. */
#define ATXPWRON_PORT PORTF
/** ATX POWER ON pins register. */
#define ATXPWRON_PIN  PINF
/** ATX POWER ON direction register. */
#define ATXPWRON_DDR  DDRF

/** SOFT RESET pin number. */
#define SOFTRES      PC7
/** SOFT RESET port register. */
#define SOFTRES_PORT PORTC
/** SOFT RESET pins register. */
#define SOFTRES_PIN  PINC
/** SOFT RESET direction register. */
#define SOFTRES_DDR  DDRC

/** NMI pin number*/
#define NMI          PC6
/** NMI port register. */
#define NMI_PORT     PORTC
/** NMI pins register. */
#define NMI_PIN  PINC
/** NMI direction register. */
#define NMI_DDR  DDRC

/** JOYSTICK RIGHT pin number. */
#define JOYSTICK_RIGHT PG0
/** JOYSTICK LEFT pin number. */
#define JOYSTICK_LEFT  PG1
/** JOYSTICK DOWN pin number. */
#define JOYSTICK_DOWN  PG2
/** JOYSTICK UP pin number. */
#define JOYSTICK_UP    PG3
/** JOYSTICK FIRE pin number. */
#define JOYSTICK_FIRE  PG4
/** JOYSTICK pins mask. */
#define JOYSTICK_MASK  ((1<<JOYSTICK_RIGHT)|(1<<JOYSTICK_LEFT)|(1<<JOYSTICK_UP)|(1<<JOYSTICK_DOWN)|(1<<JOYSTICK_FIRE))
/** JOYSTICK port register. */
#define JOYSTICK_PORT  PORTG
/** JOYSTICK pins register. */
#define JOYSTICK_PIN   PING
/** JOYSTICK direction register. */
#define JOYSTICK_DDR   DDRC

/** RS232 CTS pin number. */
#define RS232CTS PB6
/** RS232 CTS port register. */
#define RS232CTS_PORT PORTB
/** RS232 CTS pins register. */
#define RS232CTS_PIN  PINB
/** RS232 CTS direction register. */
#define RS232CTS_DDR  DDRB

/** RS232 RTS pin number. */
#define RS232RTS PD5
/** RS232 RTS port register. */
#define RS232RTS_PORT PORTD
/** RS232 RTS pins register. */
#define RS232RTS_PIN  PIND
/** RS232 RTS direction register. */
#define RS232RTS_DDR  DDRD

/** SD write protection detect pin number. */
#define SDWRP       PB4
/** SD card detect pin number. */
#define SDDET       PB5
/** SD port register. */
#define SD_PORT PORTB
/** SD pins register. */
#define SD_PIN  PINB
/** SD detect direction register. */
#define SD_DDR  DDRB

#endif

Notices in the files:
kicad/rev_d/eva.kicad_pcb:
(C) 2011
